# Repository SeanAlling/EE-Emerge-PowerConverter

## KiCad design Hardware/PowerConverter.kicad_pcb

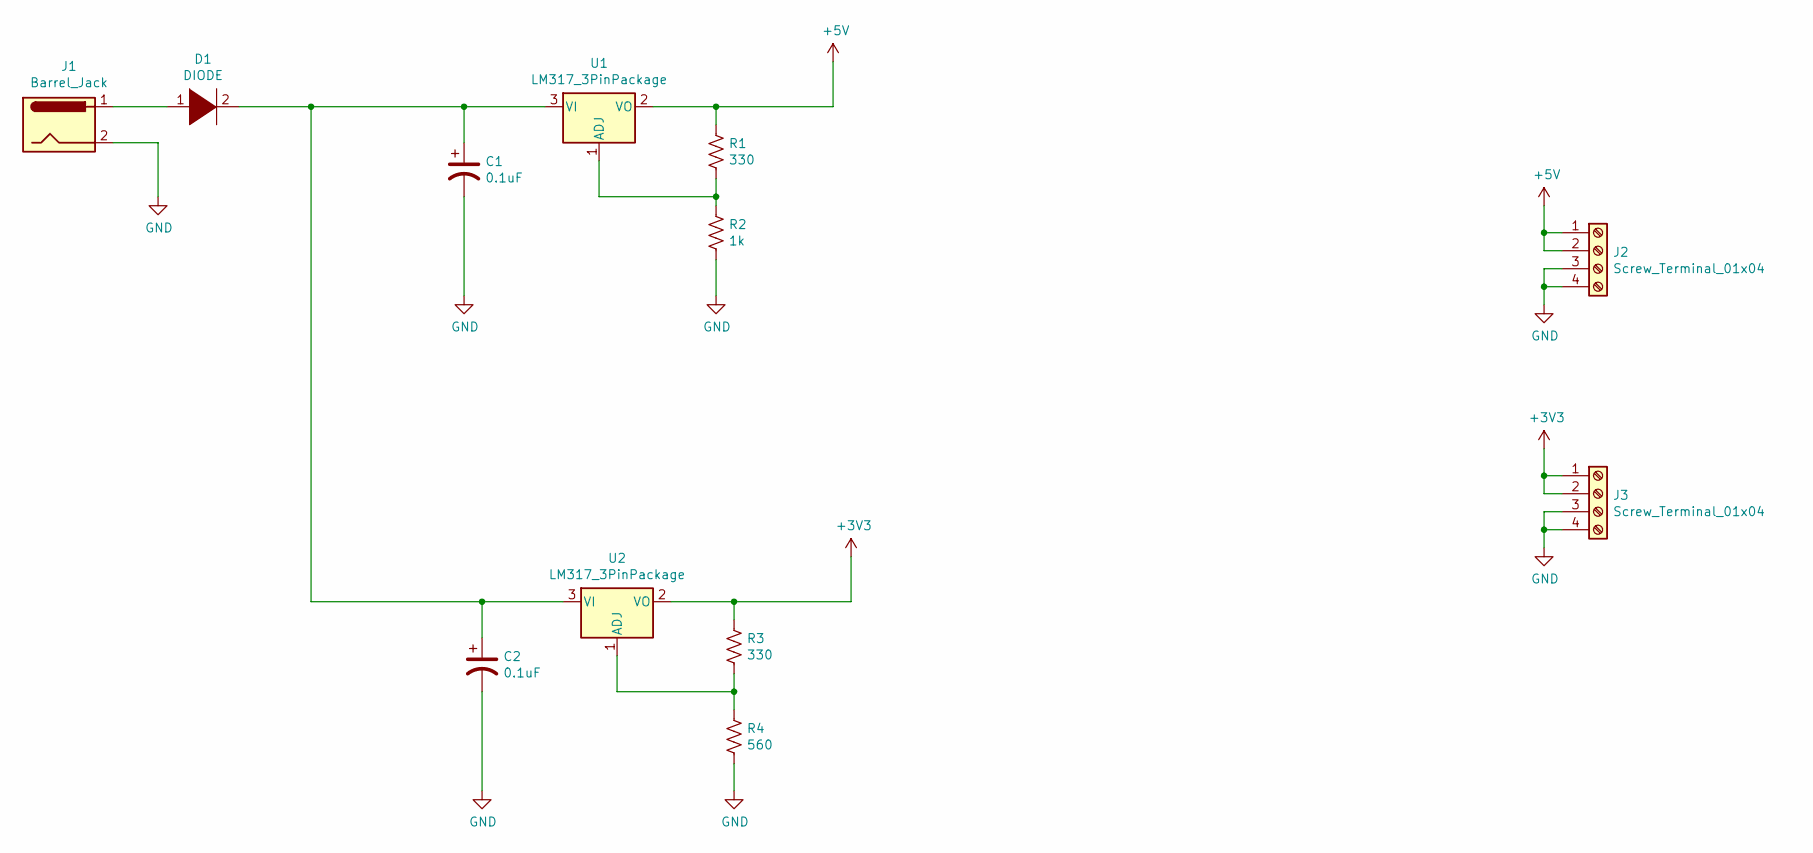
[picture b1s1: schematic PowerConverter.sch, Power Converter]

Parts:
C1, C2: 0.1uF; CP_Elec_4x4.5; mpn 865230640001; digikey# 732-8266-1-ND
D1: DIODE; D_SMB
J1: Barrel_Jack; BarrelJack_CUI_PJ-102AH_Horizontal; digikey# CP-102B-ND
J2, J3: Screw_Terminal_01x04; TerminalBlock_4Ucon_1x04_P3.50mm_Horizontal; digikey# 277-5744-ND
R1, R3: 330; R_1206_3216Metric; digikey# CR1206-FX-3300ELFCT-ND
R2: 1k; R_1206_3216Metric; digikey# RNCP1206FTD1K00CT-ND
R4: 560; R_1206_3216Metric; digikey# A129549CT-ND
U1: LM317_3PinPackage; mpn LM340SX-5.0/NOPB; digikey# LM340SX-5.0/NOPBCT-ND
U2: LM317_3PinPackage; mpn TPS7A4533KTTR; digikey# 296-23755-1-ND

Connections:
+3V3: J3.1, J3.2, R3.1, U2.2 (VO)
+5V: J2.1, J2.2, R1.1, U1.2 (VO)
GND: C1.2, C2.2, J1.2, J2.3, J2.4, J3.3, J3.4, R2.2, R4.2
unnamed: C1.1, C2.1, D1.2 (A), U1.3 (VI), U2.3 (VI)
unnamed: D1.1 (K), J1.1
unnamed: R1.2, R2.1, U1.1 (ADJ)
unnamed: R3.2, R4.1, U2.1 (ADJ)

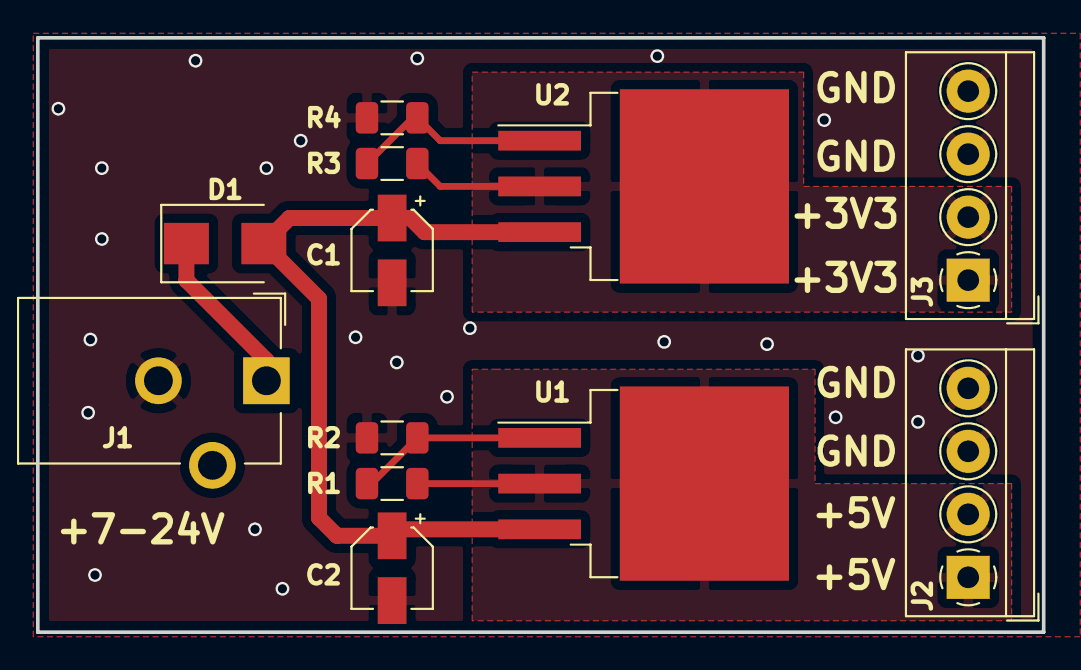
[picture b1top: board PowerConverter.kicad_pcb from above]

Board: 2 copper layers, 55.9 x 33.0 mm, 12 parts (0 on the bottom side), 7 nets.

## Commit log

2020-02-29 inital commit
2020-02-29 Initial release for V1
